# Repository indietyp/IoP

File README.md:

# Internet of Plants
## milestones for IoP development

- [x] add slave mode
- [x] use esp8266 module
- [x] change registration to active in frontend
- [x] add global settings layout
- [x] extend mesh_network + rest_api
- [x] add water pump
- [ ] rewrite setup with frontend, instead of CLI
- [ ] installation guide
- [ ] documentation

## What is Internet of Plants?
----

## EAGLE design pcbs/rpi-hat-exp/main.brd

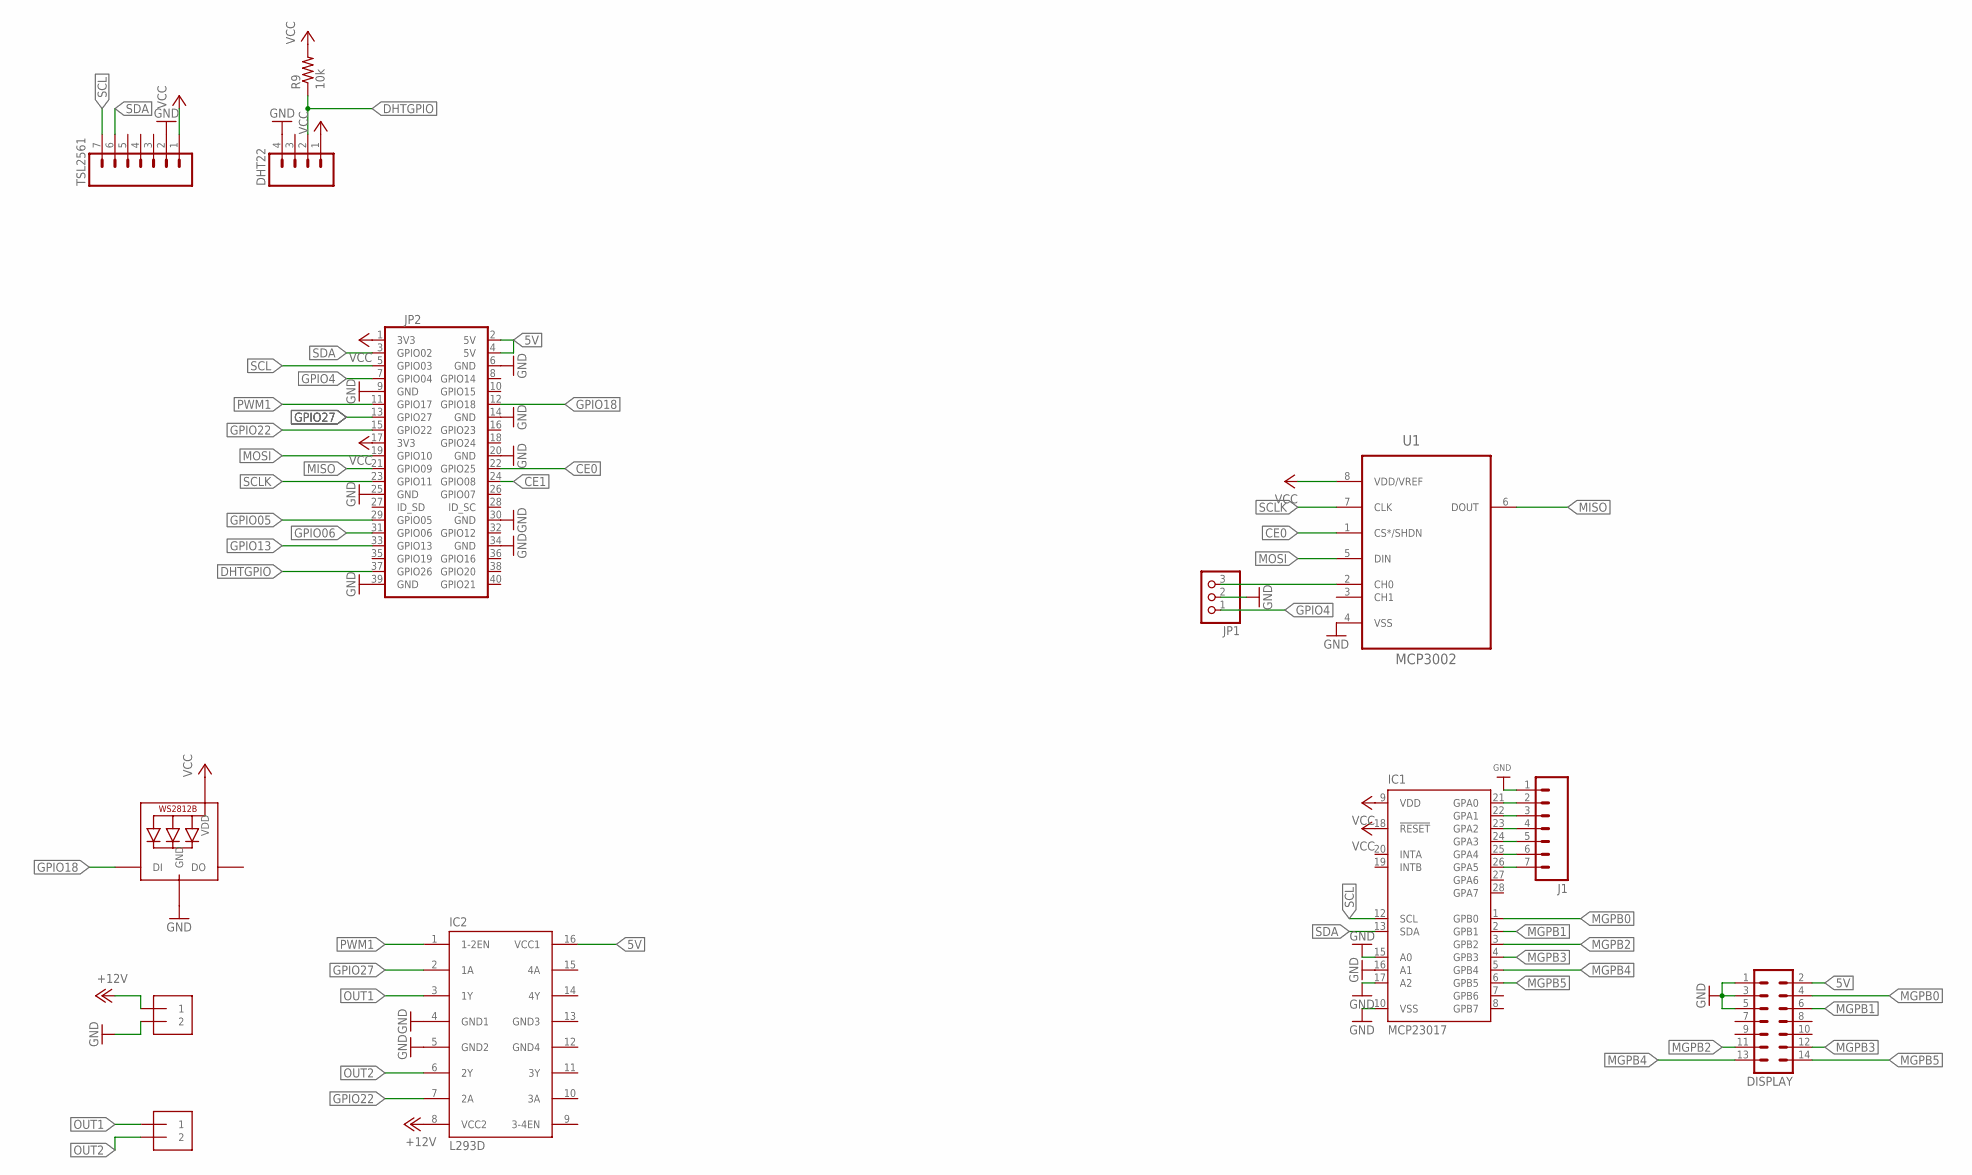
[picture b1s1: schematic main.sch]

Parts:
DHT22: M041X04_NO_SILK; 1X04_NO_SILK
DISPLAY: MA07-2
IC1: MCP23017; DIL28-3-ROUND
IC2: L293D; DIL16
J1: M07; 1X07
J2, J3: 1X2-3.5MM
JP1: PINHD-1X3; 1X03
JP2: 40W_PI_HAT_TPH; 2X20
LED2: WS2812BTH; LED5MMRGB
R9: 10k; 0204/7
TSL2561: M07NO_SILK; 1X07_NO_SILK
U1: MCP3002; DIP254P762X533-8

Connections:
5V: DISPLAY.2, IC2.16 (VCC1), JP2.2 (5V), JP2.4 (5V)
+12V: IC2.8 (VCC2), J2.1
CE0: JP2.22 (GPIO25), U1.1 (CS*/SHDN)
CE1: JP2.24 (GPIO08)
DHTGPIO: DHT22.2, JP2.37 (GPIO26), R9.1
GND: DHT22.4, DISPLAY.1, DISPLAY.3, DISPLAY.5, IC1.10 (VSS), IC1.15 (A0), IC1.16 (A1), IC1.17 (A2), IC2.4 (GND1), IC2.5 (GND2), J1.1, J2.2, JP1.2, JP2.6 (GND), JP2.9 (GND), JP2.14 (GND), JP2.20 (GND), JP2.25 (GND), JP2.30 (GND), JP2.34 (GND), JP2.39 (GND), LED2.2 (GND), TSL2561.2, U1.4 (VSS)
GND3: IC2.13 (GND3)
GND4: IC2.12 (GND4)
GPIO4: JP1.1, JP2.7 (GPIO04)
GPIO05: JP2.29 (GPIO05)
GPIO06: JP2.31 (GPIO06)
GPIO13: JP2.33 (GPIO13)
GPIO18: JP2.12 (GPIO18), LED2.4 (DI)
GPIO22: IC2.7 (2A), JP2.15 (GPIO22)
GPIO27: IC2.2 (1A), JP2.13 (GPIO27)
MGPB0: DISPLAY.4, IC1.1 (GPB0)
MGPB1: DISPLAY.6, IC1.2 (GPB1)
MGPB2: DISPLAY.11, IC1.3 (GPB2)
MGPB3: DISPLAY.12, IC1.4 (GPB3)
MGPB4: DISPLAY.13, IC1.5 (GPB4)
MGPB5: DISPLAY.14, IC1.6 (GPB5)
MISO: JP2.21 (GPIO09), U1.6 (DOUT)
MOSI: JP2.19 (GPIO10), U1.5 (DIN)
unnamed: IC1.26 (GPA5), J1.7
unnamed: IC1.25 (GPA4), J1.6
unnamed: IC1.24 (GPA3), J1.5
unnamed: IC1.23 (GPA2), J1.4
unnamed: IC1.22 (GPA1), J1.3
unnamed: JP1.3, U1.2 (CH0)
unnamed: IC1.21 (GPA0), J1.2
OUT1: IC2.3 (1Y), J3.1
OUT2: IC2.6 (2Y), J3.2
PWM1: IC2.1 (1-2EN), JP2.11 (GPIO17)
SCL: IC1.12 (SCL), JP2.5 (GPIO03), TSL2561.7
SCLK: JP2.23 (GPIO11), U1.7 (CLK)
SDA: IC1.13 (SDA), JP2.3 (GPIO02), TSL2561.6
VCC: DHT22.1, IC1.9 (VDD), IC1.18 (!RESET), JP2.1 (3V3), JP2.17 (3V3), LED2.3 (VDD), R9.2, TSL2561.1, U1.8 (VDD/VREF)

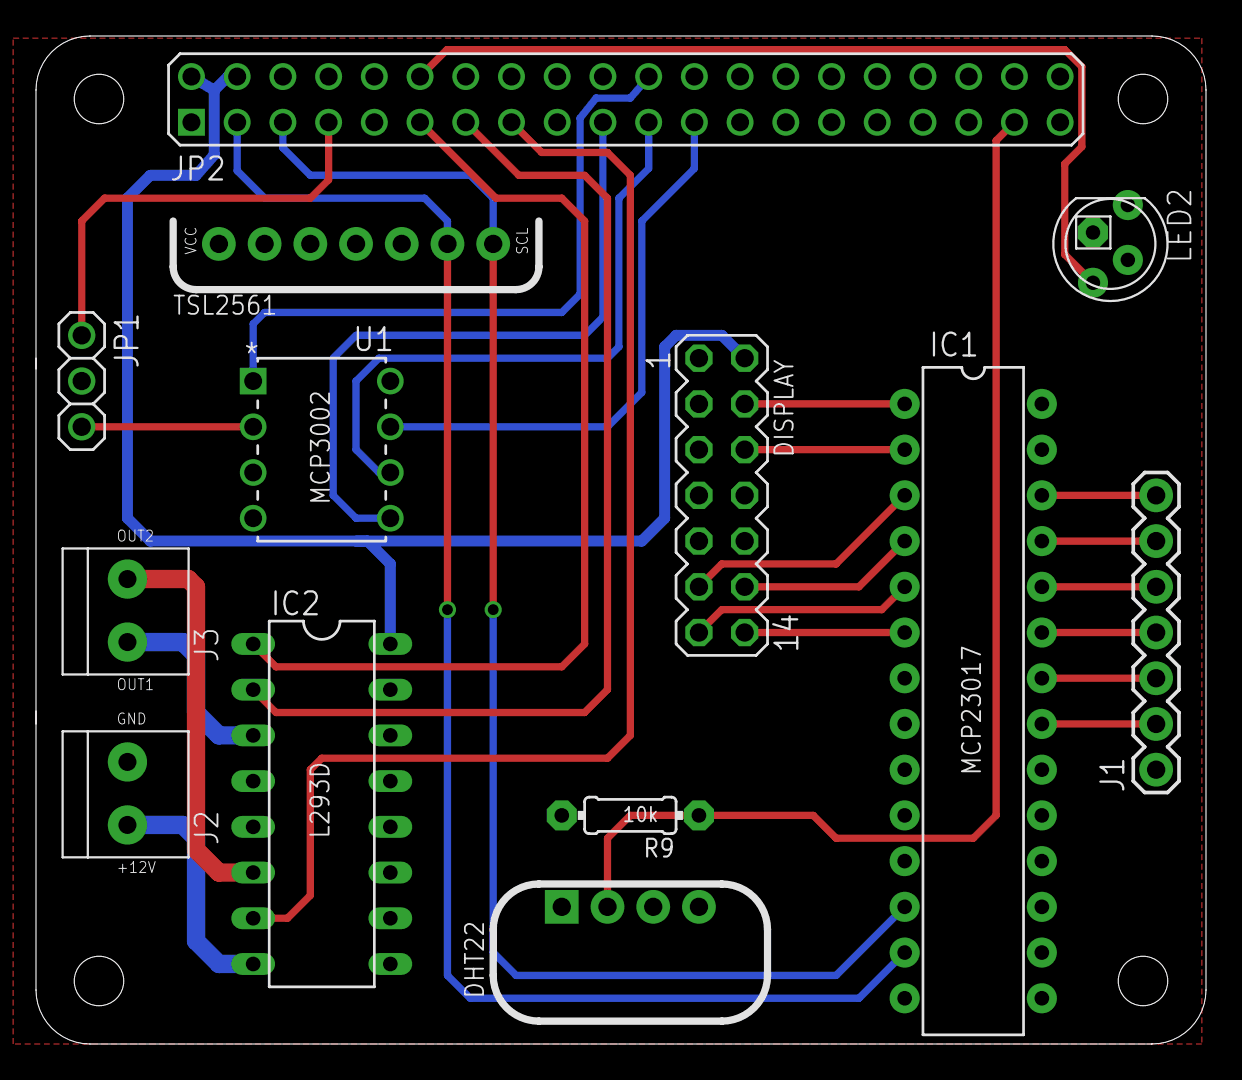
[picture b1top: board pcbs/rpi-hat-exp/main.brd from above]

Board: 2 copper layers, 65.0 x 56.0 mm, 14 parts (0 on the bottom side), 31 nets.

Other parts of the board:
U$3: PI_HAT_STANDARD_TPH

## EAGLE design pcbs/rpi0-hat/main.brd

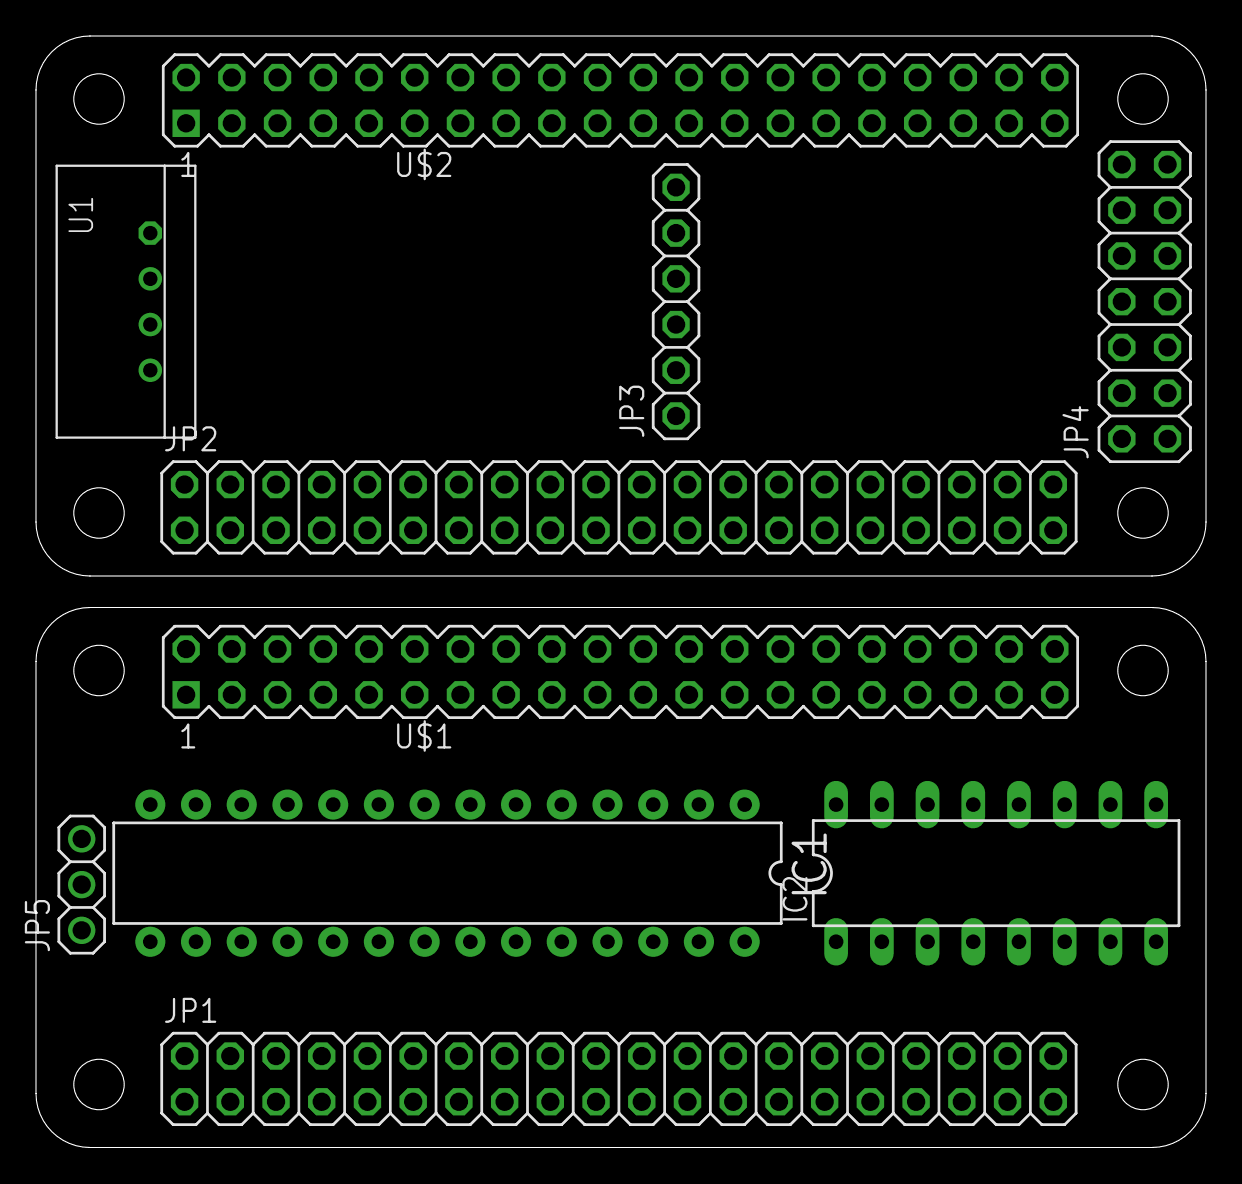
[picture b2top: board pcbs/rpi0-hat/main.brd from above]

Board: 2 copper layers, 65.0 x 61.8 mm, 10 parts (0 on the bottom side), 2 nets, no tracks yet.

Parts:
IC1: MCP23017SP2; DIL28-3-ROUND
IC2: MCP3008; DIL16
JP1, JP2: 2X20
JP3: 1X06
JP4: 2X07
JP5: 1X03
U1: RHT03_DHT-22
U$1, U$2: PIZERO_THROUGH_HOLE; PIZERO_THOUGH_HOLE

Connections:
GND: IC2.9, U1.GND
VDD: IC1.9, IC2.16, U1.VDD

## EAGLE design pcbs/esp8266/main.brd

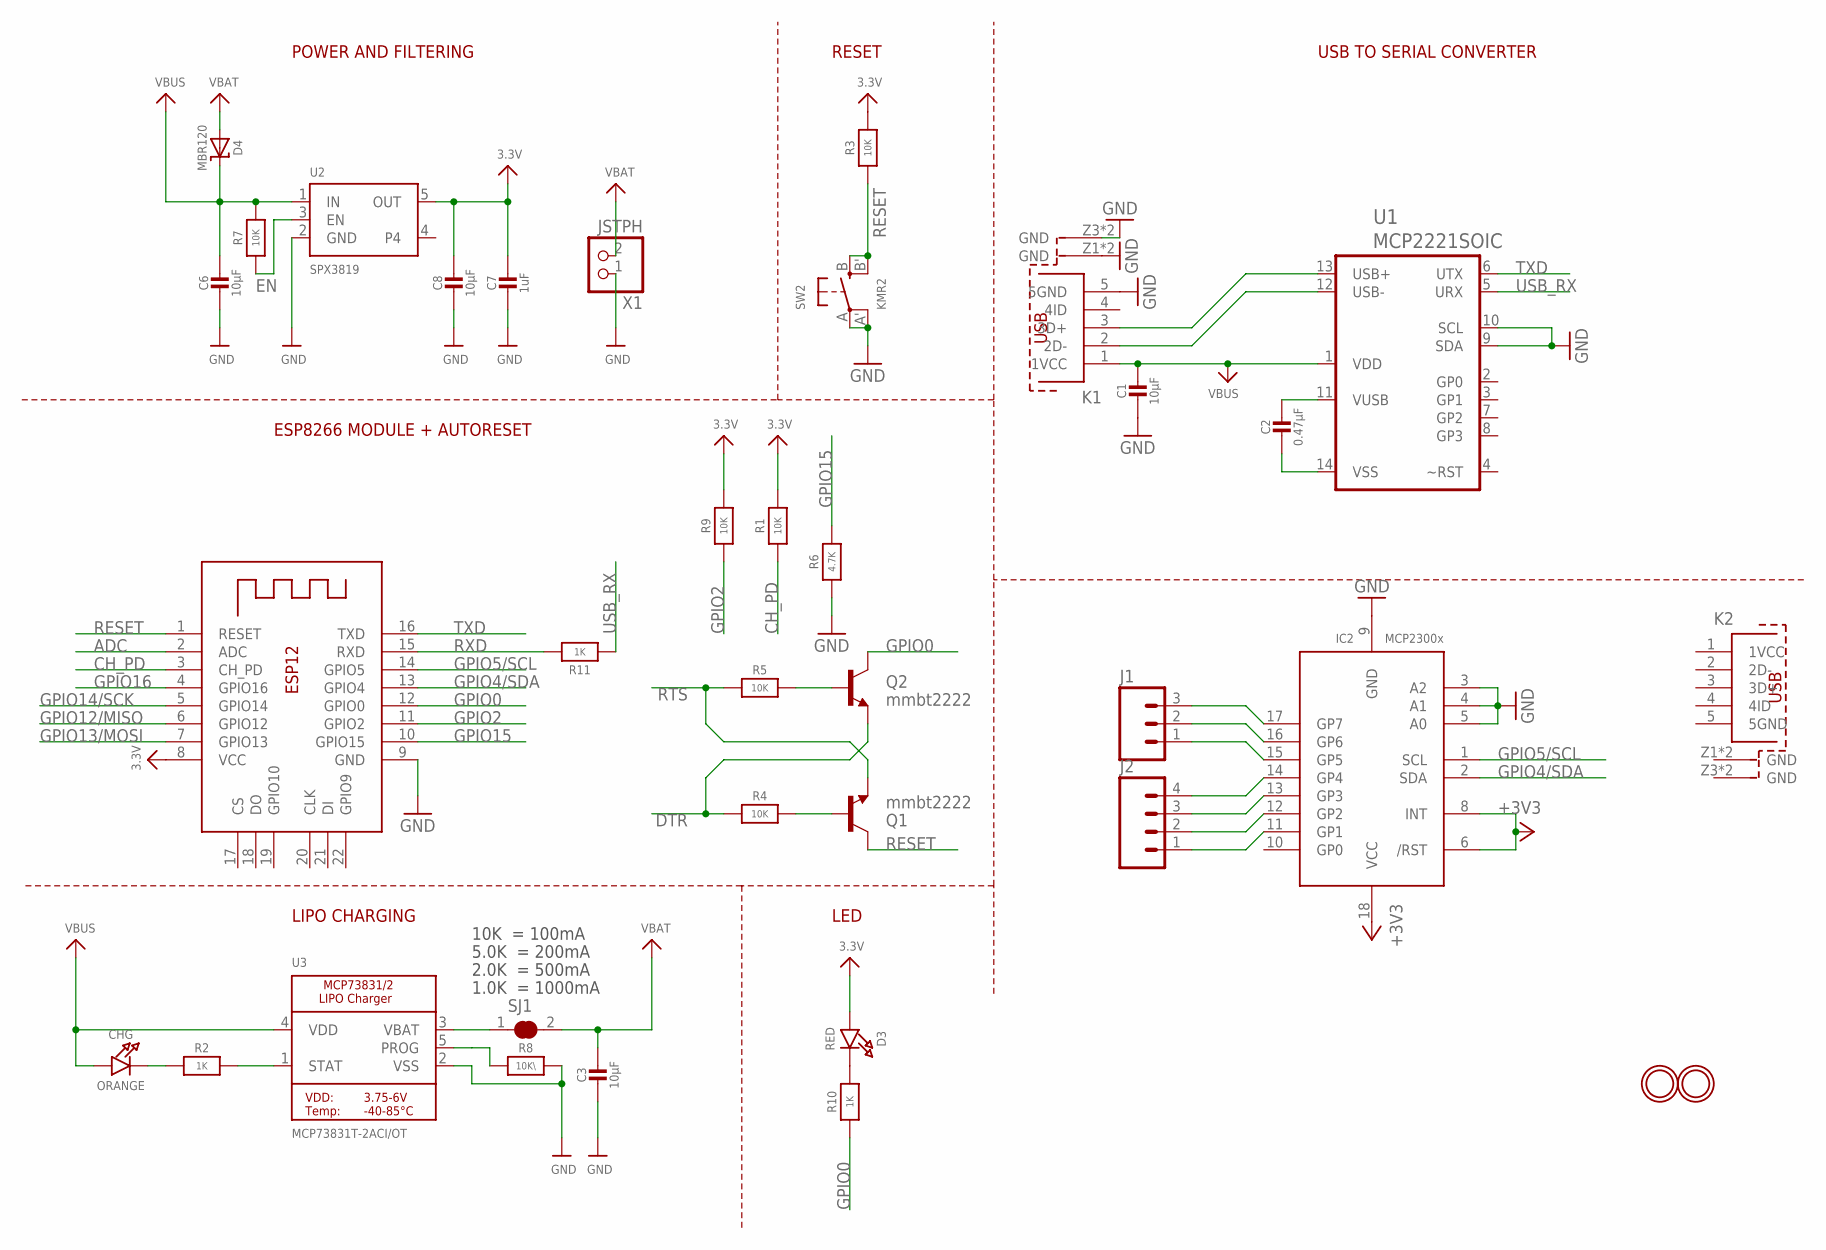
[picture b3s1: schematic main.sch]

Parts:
C1, C3, C6, C8: 10µF; 0805-NO
C2: 0.47µF; 0805-NO
C7: 1uF; 0603-NO
CHG: ORANGE; CHIPLED_0805_NOOUTLINE
D3: RED; CHIPLED_0805_NOOUTLINE
D4: MBR120; SOD-123
IC2: MCP23008/SO; SO18W
J1: M031X03_NO_SILK; 1X03_NO_SILK
J2: M04NO_SILK_ALL_ROUND; 1X04_NO_SILK_ALL_ROUND
K1, K2: 629105150521
Q1, Q2: mmbt2222; SOT23-3
R1, R3, R4, R7, R9: 10K; 0603-NO
R2, R10: 1K; 0603-NO
R5: 10K; _0603MP
R6: 4.7K; 0603-NO
R8: 10K\; 0603-NO
R11: 1K; _0603MP
SJ1: SOLDERJUMPER_CLOSED; SOLDERJUMPER_CLOSEDWIRE
SW2: KMR2; BTN_KMR2_4.6X2.8
U1: MCP2221SOIC; SOIC14
U2: SPX3819; SOT23-5
U3: MCP73831T-2ACI/OT; SOT23-5
U$31, U$32: MOUNTINGHOLE2.5; MOUNTINGHOLE_2.5_PLATED
X1: JSTPH; JSTPH2
X2: ESP-12; ESP-12E

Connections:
3.3V: C7.1, C8.1, D3.A, R1.2, R3.2, R9.2, U2.5 (OUT), X2.8 (VCC)
+3V3: IC2.6 (/RST), IC2.8 (INT), IC2.18 (VCC)
ADC: X2.2 (ADC)
CH_PD: R1.1, X2.3 (CH_PD)
DTR: Q2.2 (E), R4.1
EN: R7.1, U2.3 (EN)
GND: C1.2, C3.2, C6.2, C7.2, C8.2, IC2.3 (A2), IC2.4 (A1), IC2.5 (A0), IC2.9 (GND), K1.5 (5GND), K1.Z1 (GND), K1.Z2 (GND), K1.Z3 (GND), K1.Z4 (GND), R6.1, R8.2, SW2.A, SW2.A' (P1), U1.9 (SDA), U1.10 (SCL), U2.2 (GND), U3.2 (VSS), X1.1, X2.9 (GND)
GPIO0: Q2.3 (C), R10.1, X2.12 (GPIO0)
GPIO2: R9.1, X2.11 (GPIO2)
GPIO4/SDA: IC2.2 (SDA), X2.13 (GPIO4)
GPIO5/SCL: IC2.1 (SCL), X2.14 (GPIO5)
GPIO12/MISO: X2.6 (GPIO12)
GPIO13/MOSI: X2.7 (GPIO13)
GPIO14/SCK: X2.5 (GPIO14)
GPIO15: R6.2, X2.10 (GPIO15)
GPIO16: X2.4 (GPIO16)
unnamed: CHG.C, R2.1
unnamed: C2.1, U1.11 (VUSB)
unnamed: R2.2, U3.1 (STAT)
unnamed: R8.1, U3.5 (PROG)
unnamed: D3.C, R10.2
unnamed: C2.2, U1.14 (VSS)
unnamed: SJ1.1, U3.3 (VBAT)
unnamed: K1.3 (3D+), U1.13 (USB+)
unnamed: IC2.17 (GP7), J1.3
unnamed: IC2.16 (GP6), J1.2
unnamed: IC2.15 (GP5), J1.1
unnamed: Q1.1 (B), R4.2
unnamed: Q2.1 (B), R5.2
unnamed: IC2.14 (GP4), J2.4
unnamed: IC2.13 (GP3), J2.3
unnamed: IC2.12 (GP2), J2.2
unnamed: IC2.11 (GP1), J2.1
unnamed: K1.2 (2D-), U1.12 (USB-)
RESET: Q1.3 (C), R3.1, SW2.B (S), SW2.B' (S1), X2.1 (RESET)
RTS: Q1.2 (E), R5.1
RXD: R11.2, X2.15 (RXD)
TXD: U1.6 (UTX), X2.16 (TXD)
USB_RX: R11.1, U1.5 (URX)
VBAT: C3.1, D4.A, SJ1.2, X1.2
VBUS: C1.1, C6.1, CHG.A, D4.C, K1.1 (1VCC), R7.2, U1.1 (VDD), U2.1 (IN), U3.4 (VDD)

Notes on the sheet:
POWER AND FILTERING
RESET
10K = 100mA
5.0K = 200mA
2.0K = 500mA
1.0K = 1000mA
USB TO SERIAL CONVERTER
LIPO CHARGING
LED
ESP8266 MODULE + AUTORESET

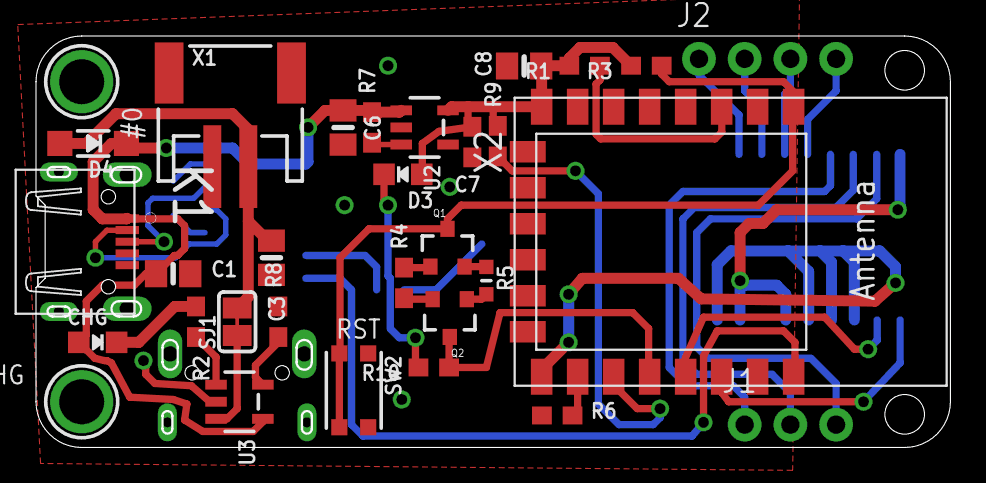
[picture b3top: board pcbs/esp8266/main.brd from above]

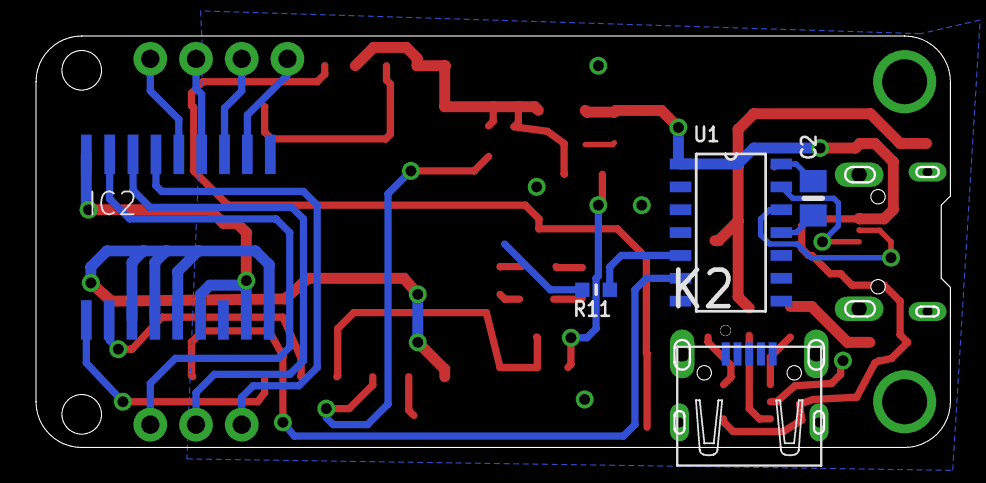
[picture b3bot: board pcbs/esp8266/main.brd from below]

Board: 2 copper layers, 50.7 x 22.7 mm, 36 parts (5 on the bottom side), 36 nets.

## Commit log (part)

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2016-03-19 minor changes
2016-03-19 inserted protocol correctly
2016-03-19 added readme
2016-03-19 relaunch number 2
2016-03-19 daemon now working
2016-03-21 interval now regulated in frontend
2016-03-21 fixed and added general status leds
2016-03-25 minor changes + added service of uwsgi
2016-03-25 added testcase
2016-03-25 minor fixes
2016-03-25 bug fixes, partly finished testcase
2016-03-31 added keychain + mesh network
2016-03-31 fixed dht
2016-03-31 changed minor stuff
2016-03-31 added mesh fix
2016-04-01 added complete REST integration
2016-05-26 moved to backend
2016-05-26 reverting commit
2016-05-26 moved sensor_scripts
2016-05-26 moved to rest_api
2016-05-26 moved mesh_network
2016-05-26 added pcbs and frontend
2016-05-26 concept notification settings
2016-05-30 modified plant settings
2016-06-01 changes in global settings design
2016-06-05 added first Singe Page Apllication things and minor changes
2016-06-08 fixed pie chart, minor changes, css -> less, extended single page functionality
2016-06-13 added online data to overview script, spa extended, rest_api -> many get stuff + first unittests! <3
2016-06-15 sensor + overview now full functionality, next settings!
2016-06-20 moved functions to JQUERY, completed get information for plant overview, started plant settings
2016-06-21 added readout plant_settings and update non specific stuff
2016-06-23 added concept rpi0-hat, completed plant_settings, added forecast
2016-06-23 removed old forecast
2016-06-24 significant time change forecast
2016-06-24 added response testcase 502.173333333 average at 150th fail, added graph forecast
2016-06-26 added first daemon concept
2016-06-26 changed DHT to class
2016-08-18 big changes are coming, redesign database and reworking
2016-08-21 fixed display
2016-08-25 regression
2016-08-28 changing mesh_network
2016-09-10 ported website - rest_api - meshnetwork new
2016-09-10 registration changes
2016-09-15 finishing touches in mesh_network -> only remains new_data, started dedicated, tested package send rate - ex. ALIVE 19.6 packages/sec, 0 lost in 50 sec (huge improvement)
2016-09-20 frontend add plant
2016-09-20 added requirements.txt
2016-09-20 updated requirements.txt
2016-09-24 frontend improvments and simlated dedicated in working
2016-10-21 added message presets, speed up, -> todo
2016-11-03 added message presets in frontend and people management
2016-11-12 ref todo! (frontend working & create plant)
2016-11-14 ref main.todo sum: added emoji, simulated & mirror minor settings
2016-11-16 added overview
2016-11-20 ref todo - added duration plant sliders and modified fields
    reminder to myself: more and smaller commits
2016-11-21 ref todo
2016-12-16 prepared for move
2016-12-17 tested
2016-12-17 for testing
2016-12-17 testing insert database
2016-12-17 fixes
2016-12-17 fix?
2016-12-17 fix!
2016-12-17 hardware display fix
2016-12-17 cheating, sry :o
2016-12-17 database day nicht time fix
2016-12-17 bla bli blu
2016-12-17 something seems to be wrong with the i2c handling in moisture bar
2016-12-18 fixes!
2016-12-18 rest api datetime fix?
2016-12-18 hotfix!
2016-12-18 hothotfix
2016-12-18 very hot fix
2016-12-19 added meinheld
2016-12-19 test
2016-12-19 huge speedup rest_api start/stop
2016-12-19 predicting speedup
2016-12-20 added time measure
2016-12-21 daemon startup
2016-12-21 added changing ip! YEAY
2016-12-21 mesh_netowrk test successfull
2016-12-21 daemon
2016-12-21 added smarter daemon?
2016-12-21 testing faster method
2016-12-21 too many inserts fix!
2016-12-21 testing
2016-12-23 display fix
2016-12-24 preparing plant-simulate
2016-12-24 fixes?
2016-12-24 speedup fix
2016-12-25 changes todo
2016-12-26 added simulated pi stage to production todo list and no database improvement
2016-12-26 gitignore change
2016-12-27 added host field
2016-12-28 added speedup and fixes
2016-12-28 frontend predicted change
2016-12-28 .gitignore is now working
2016-12-28 changes!
2016-12-29 aha!
2016-12-29 added debug defaul and changes insert to proper handling
2016-12-29 fixed
2016-12-29 first draft - needs rework - simulated
2016-12-30 fancy changes - simulated plant and retirement json_util
2016-12-31 simulate plant
2016-12-31 simulate
2017-01-01 database locking fixes
2017-01-02 fixed simulated
2017-01-02 big logging change!
2017-01-02 additional logging
2017-01-02 simulated change
2017-01-02 logging
2017-01-02 w/o testing sensor improvements - now time dependent
2017-01-02 logging!
2017-01-02 logging?
2017-01-02 forecast! limit to 144
2017-01-02 fighting against ProgrammingError! AAAAAH
2017-01-03 time consumption logging
2017-01-03 computing time logging
2017-01-03 fixes w/o testing
2017-01-03 hotFIX
2017-01-03 POST
2017-01-03 import fix
2017-01-04 staging!
2017-01-04 speed up and satisfaction changes
2017-01-04 logging FUCK YEAH!
2017-01-04 sat_streak fix
2017-01-07 mail rework
2017-01-07 satisfaction fix
2017-01-08 file upload preperation
2017-01-08 return fix
2017-01-08 return fix & file upload
2017-01-09 file fix
2017-01-09 plant image support w/o testing
2017-01-09 fixed profile upload
2017-01-09 image support settings seeable
2017-01-09 /get/picture/plant
2017-01-09 integrating changes
2017-01-11 offline fix
2017-01-11 changing todo
2017-01-11 change alive mode
2017-01-11 get_or_create fix
2017-01-11 moving the magic _
2017-01-15 slave micropython testing
2017-01-17 slave http & boot done
2017-01-22 migrations!
2017-01-22 frontend change
2017-01-23 frontend changes
2017-01-23 frontend fix
2017-01-23 frontend reintegration
2017-01-23 js fix
2017-01-23 asdwad
2017-01-24 hello johannes!
2017-01-24 master selection toggle
2017-01-24 again...
2017-01-24 slave register reintegration
2017-01-24 register changes
2017-01-24 dedicated register testing change
2017-01-24 changes to the mesh infrastructure
2017-01-24 master vs! slave
    who wins?
2017-01-24 hahaha! YOU FOOL
2017-01-24 fancy pants changes
2017-01-24 mesh fixes
2017-01-24 uuid fix
2017-01-25 retrieve and insert slave data
2017-01-25 daemon slave changes
2017-01-25 added dedicated & sensor integration
2017-01-25 return change
2017-01-25 100degree hotfix
2017-01-26 rest_api slave change
2017-01-27 update slave alive
2017-01-27 update update
2017-01-27 update rename
2017-01-27 alive slave compatible
2017-01-27 alive test
2017-01-27 alive deepcopy change
2017-01-27 changing stupid deepcopy change
2017-01-27 less debug output
2017-01-27 added more vebose logging
2017-01-29 added slave update & first mesh template
2017-01-29 quick redirect fix
2017-01-29 experimentation
2017-01-29 mwhahahahaha spamming commits
2017-01-29 added /manage concept
2017-01-29 deliver change
2017-01-29 deliver fix
2017-01-29 update logger
2017-01-29 slave range support
2017-01-29 mesh fix
2017-01-29 update fix
2017-01-30 sensor fix
2017-02-01 master remove
2017-02-03 daemon change
2017-02-03 mesh
2017-02-05 slave, delete
2017-02-05 verbose logging, wuhu
2017-02-05 relation added
2017-02-05 added basedir
2017-02-05 smal fix
2017-02-06 append failure
2017-02-06 local integration
2017-02-06 cutting
2017-02-06 daemon fix
2017-02-06 int to str
2017-02-06 daenib verbose logging and max length messages
2017-02-06 ident fix
2017-02-06 var fix
2017-02-06 var rename
2017-02-06 the timestamp fix
2017-02-06 overflow correction
2017-02-06 list -> str
2017-02-06 list change
    btw... I hate my life...
2017-02-06 string conversion fix
2017-02-06 str -> int
2017-02-06 str --> int
2017-02-06 encoding issues
2017-02-06 tuple -> list
2017-02-06 public -> private
2017-02-07 typecheck
2017-02-07 adaw
2017-02-07 daemon verbose logging
2017-02-08 daemon check
2017-02-08 send fix
2017-02-08 adawd
2017-02-08 mwhahaha
2017-02-08 toolchain!
2017-02-08 less verbose logging
2017-02-15 mesh changes
2017-02-15 added sh scripts
2017-02-15 removed mesh_network scripts
2017-02-15 added target verification and plant import
2017-02-15 added import
2017-02-15 import -.-"
2017-02-15 mesh change
2017-02-15 changed mesh remove
2017-02-16 frontend edit
2017-02-16 frontend
2017-02-16 added response
2017-02-16 get fix
2017-02-16 changing fancy stuff
2017-02-16 singular -> plural
2017-02-16 small change
2017-02-16 debugging
2017-02-16 syntax change
2017-02-16 chung chang ching
2017-02-16 looki looki
2017-02-16 chunge
2017-02-16 regex wow
2017-02-16 change!
2017-02-16 capitalize!
2017-02-16 fast
2017-02-16 dropdown!
2017-02-16 me == dumb
2017-02-16 style fix
2017-02-16 changed icon
2017-02-17 frontend purge integration
2017-02-17 static changes
2017-02-17 interesting....
2017-02-17 (facepalm)
2017-02-17 try again!
2017-02-17 network changes
2017-02-17 host change fix
2017-02-17 added force host for debugging
2017-02-17 polishing remove
2017-02-17 new_data change
2017-02-19 cleanup + mesh level change + location href
2017-02-19 added href on remove
2017-02-19 ' fix
2017-02-19 satisfaction slave support
2017-02-19 satisfaction
2017-02-27 frontend - mesh - slave changes
2017-02-27 init dev change
2017-02-27 verification fix
2017-02-27 error
2017-02-27 daemon verification?
2017-02-28 discover return changes
2017-03-01 wuhu
2017-03-01 verbose logging
2017-03-01 obj change
2017-03-01 pahuhu
2017-03-01 fchange
2017-03-01 changes?
2017-03-01 haha!
2017-03-04 mcpchanges yeah!
2017-03-04 lib change
2017-03-04 moisture change
2017-03-04 moisture bar correction
2017-03-04 extensions!
2017-03-04 numbering change
2017-03-05 fuck
2017-03-05 mcp change
2017-03-07 external hardware fixes
2017-03-07 board changes
2017-03-07 board changes & template init finished
2017-03-07 PRAGMAS ALL DAY LONG!
2017-03-13 great changes, like the great wall of china
2017-03-13 pin change
2017-03-17 I changed 'some' stuff
2017-03-17 pump change wuhu $ board finalised
2017-03-18 neopixel test
2017-03-18 slave changes
2017-03-18 test changes
2017-03-18 changes stuff
2017-03-18 cosine -> linear
2017-03-18 linear change
2017-03-18 linear parralel
2017-03-18 changed some stuff
2017-03-18 disabled water pump
2017-03-21 printed
2017-04-02 slight slave changes and REST v4
2017-04-07 REST v4.1.0.1
    staged not official release yet
2017-04-10 4.1.0.6
2017-04-10 frontend spelling mistakes
2017-04-10 added verbose debugging logging
2017-04-10 file ending stuff changed a bit
2017-04-10 removed setup script tag
2017-04-10 init change
2017-04-12 REST v4.1 - frontend v3.2 - mesh v2.7

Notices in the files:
parts and their libraries:
microbuilder: This work is placed in the public domain, and may be freely used for commercial and non-commercial work with the following conditions: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
SparkFun: Licensing: CC v3.0 Share-Alike You are welcome to use this library for commercial purposes.
